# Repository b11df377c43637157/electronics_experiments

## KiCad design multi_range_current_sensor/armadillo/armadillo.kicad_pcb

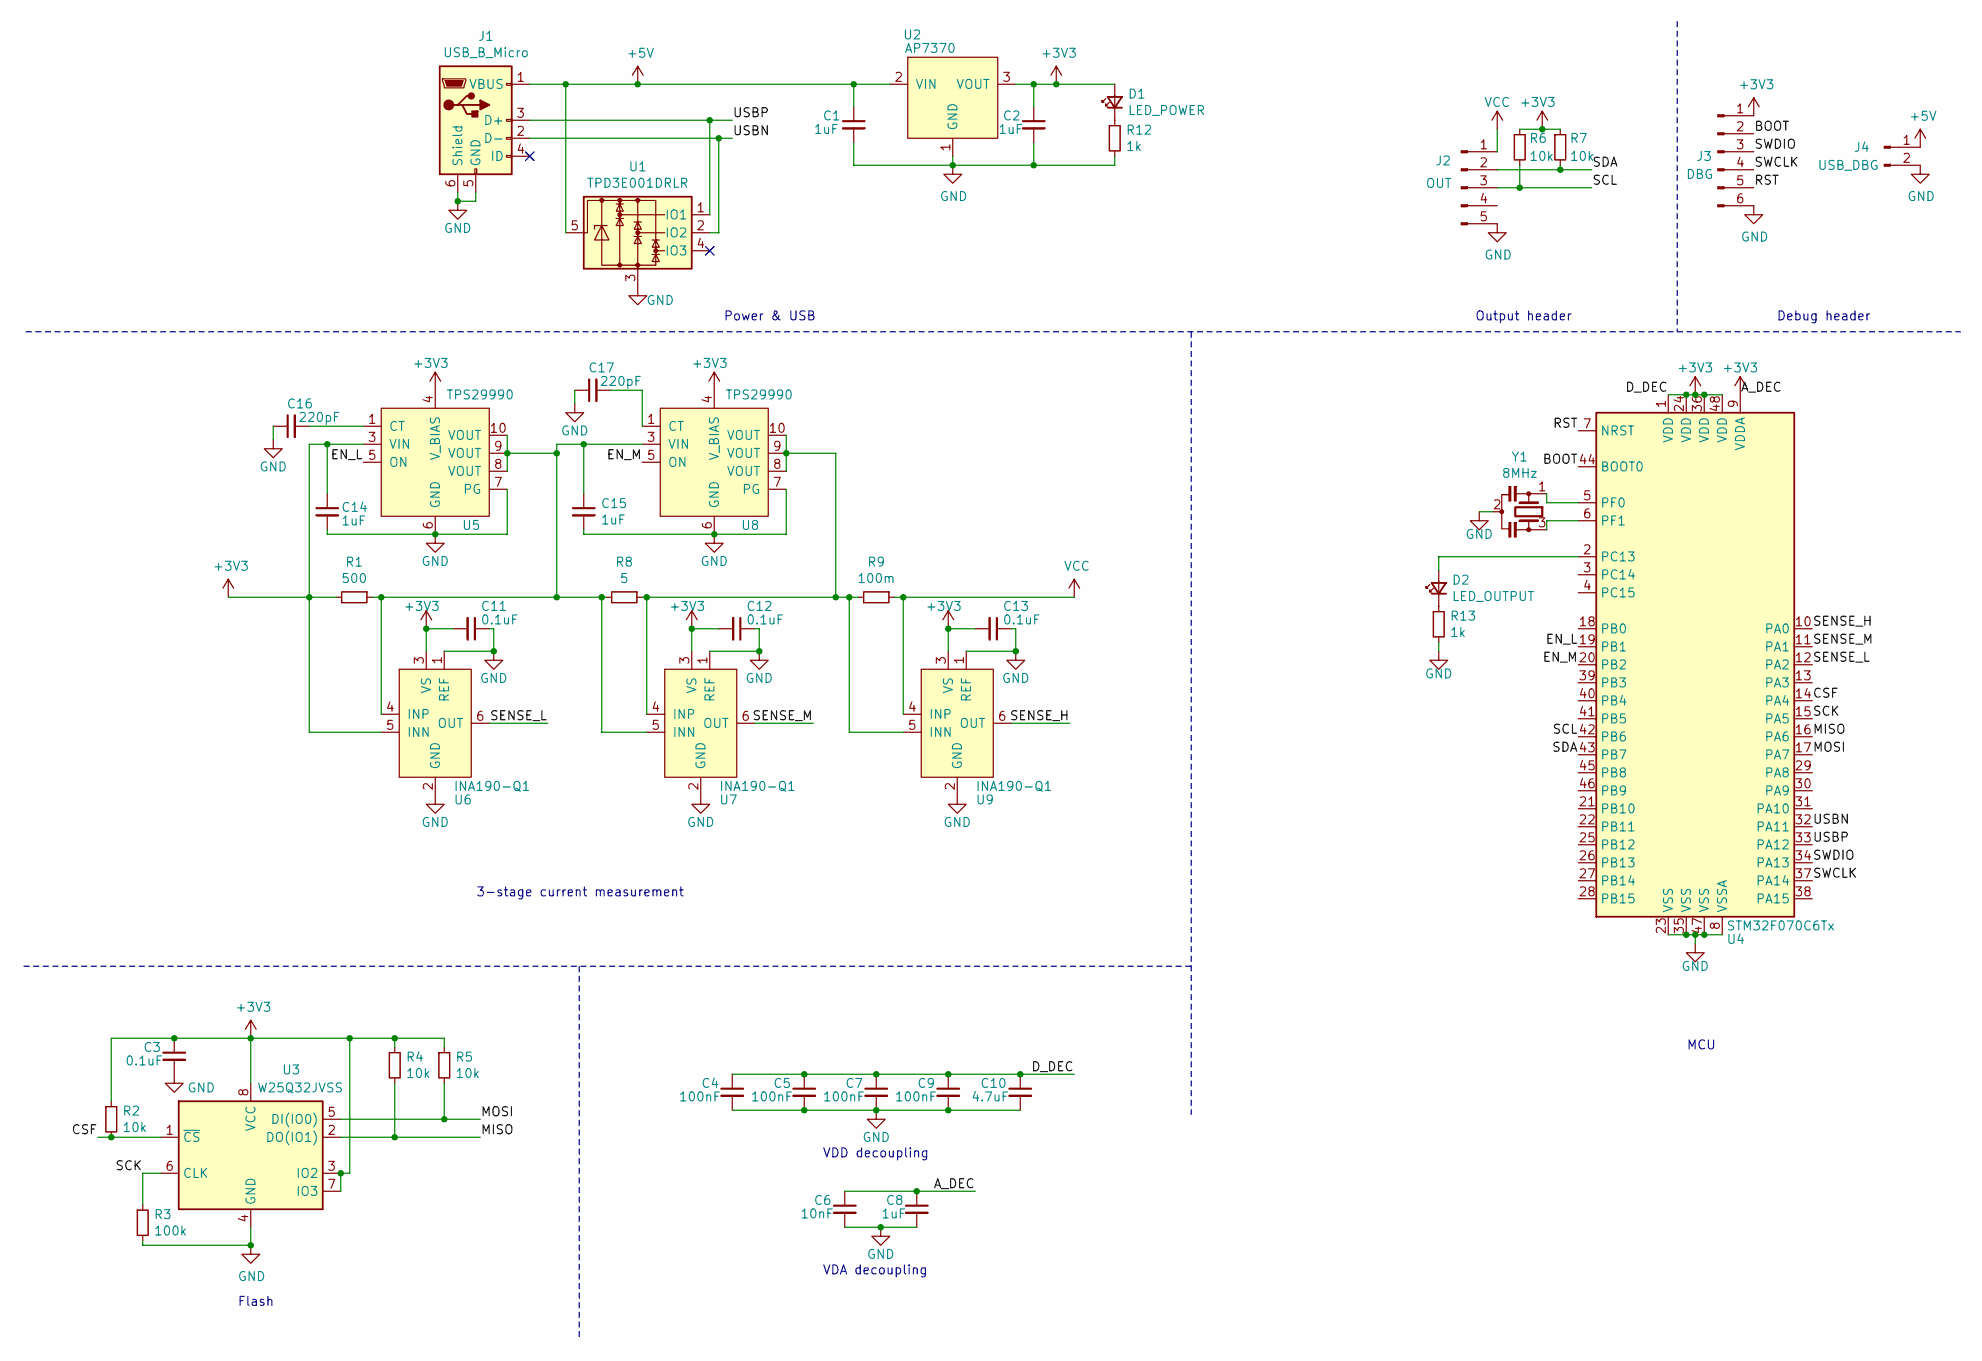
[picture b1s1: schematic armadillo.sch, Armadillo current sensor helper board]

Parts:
C1, C2, C8, C14, C15: 1uF; C_0603_1608Metric_Pad1.05x0.95mm_HandSolder
C3, C11, C12, C13: 0.1uF; C_0603_1608Metric_Pad1.05x0.95mm_HandSolder
C4, C5, C7, C9: 100nF; C_0603_1608Metric_Pad1.05x0.95mm_HandSolder
C6: 10nF; C_0603_1608Metric_Pad1.05x0.95mm_HandSolder
C10: 4.7uF; C_0603_1608Metric_Pad1.05x0.95mm_HandSolder
C16, C17: 220pF; C_0603_1608Metric_Pad1.05x0.95mm_HandSolder
D1: LED_POWER; LED_0603_1608Metric_Pad1.05x0.95mm_HandSolder
D2: LED_OUTPUT; LED_0603_1608Metric_Pad1.05x0.95mm_HandSolder
J1: USB_B_Micro; USB_Micro-B_Molex_47346-0001
J2: OUT; PinHeader_1x05_P2.54mm_Vertical
J3: DBG; PinHeader_1x06_P2.54mm_Vertical
J4: USB_DBG; PinHeader_1x02_P2.54mm_Vertical
R1: 500; R_0603_1608Metric_Pad1.05x0.95mm_HandSolder
R2, R4, R5, R6, R7: 10k; R_0603_1608Metric_Pad1.05x0.95mm_HandSolder
R3: 100k; R_0603_1608Metric_Pad1.05x0.95mm_HandSolder
R8: 5; R_0603_1608Metric_Pad1.05x0.95mm_HandSolder
R9: 100m; R_0603_1608Metric_Pad1.05x0.95mm_HandSolder
R12, R13: 1k; R_0603_1608Metric_Pad1.05x0.95mm_HandSolder
U1: TPD3E001DRLR; SOT-543
U2: AP7370; SOT-23-5_HandSoldering
U3: W25Q32JVSS; SOIC-8_5.23x5.23mm_P1.27mm
U4: STM32F070C6Tx; LQFP-48_7x7mm_P0.5mm
U5, U8: TPS29990; WSON-10-1EP_2x3mm_P0.5mm_EP0.84x2.4mm_ThermalVias
U6, U7, U9: INA190-Q1; SOT-363_SC-70-6_Handsoldering
Y1: 8MHz; Resonator_SMD_muRata_CSTxExxV-3Pin_3.0x1.1mm_HandSoldering

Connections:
+3V3: C2.1, C3.1, C4.1, C5.1, C6.1, C7.1, C8.1, C9.1, C10.1, C11.2, C12.2, C13.2, C14.1, D1.2 (A), J3.1, R1.2, R2.1, R4.1, R5.1, R6.1, R7.1, U2.3 (VOUT), U3.3 (IO2), U3.7 (IO3), U3.8 (VCC), U4.1 (VDD), U4.9 (VDDA), U4.24 (VDD), U4.36 (VDD), U4.48 (VDD), U5.3 (VIN), U5.4 (V_BIAS), U5.11, U6.3 (VS), U6.5 (INN), U7.3 (VS), U8.4 (V_BIAS), U9.3 (VS)
+5V: C1.1, J1.1 (VBUS), J4.1, U1.5, U2.2 (VIN)
/BOOT: J3.2, U4.44 (BOOT0)
/CSF: R2.2, U3.1 (~CS), U4.14 (PA4)
/EN_L: U4.19 (PB1), U5.5 (ON)
/EN_M: U4.20 (PB2), U8.5 (ON)
/MISO: R4.2, U3.2 (DO(IO1)), U4.16 (PA6)
/MOSI: R5.2, U3.5 (DI(IO0)), U4.17 (PA7)
/RST: J3.5, U4.7 (NRST)
/SCK: R3.1, U3.6 (CLK), U4.15 (PA5)
/SCL: J2.3, R6.2, U4.42 (PB6)
/SDA: J2.2, R7.2, U4.43 (PB7)
/SENSE_H: U4.10 (PA0), U9.6 (OUT)
/SENSE_L: U4.12 (PA2), U6.6 (OUT)
/SENSE_M: U4.11 (PA1), U7.6 (OUT)
/SWCLK: J3.4, U4.37 (PA14)
/SWDIO: J3.3, U4.34 (PA13)
/USBN: J1.2 (D-), U1.2 (IO2), U4.32 (PA11)
/USBP: J1.3 (D+), U1.1 (IO1), U4.33 (PA12)
GND: C1.2, C2.2, C3.2, C4.2, C5.2, C6.2, C7.2, C8.2, C9.2, C10.2, C11.1, C12.1, C13.1, C14.2, C15.2, C16.1, C17.1, J1.5 (GND), J1.6 (Shield), J2.5, J3.6, J4.2, R3.2, R12.2, R13.2, U1.3, U2.1 (GND), U3.4 (GND), U4.8 (VSSA), U4.23 (VSS), U4.35 (VSS), U4.47 (VSS), U5.6 (GND), U5.7 (PG), U6.1 (REF), U6.2 (GND), U7.1 (REF), U7.2 (GND), U8.6 (GND), U8.7 (PG), U9.1 (REF), U9.2 (GND), Y1.2
unnamed: C15.1, R1.1, R8.2, U5.8 (VOUT), U5.9 (VOUT), U5.10 (VOUT), U6.4 (INP), U7.5 (INN), U8.3 (VIN), U8.11
unnamed: C16.2, U5.1 (CT)
unnamed: C17.2, U8.1 (CT)
unnamed: D1.1 (K), R12.1
unnamed: D2.1 (K), R13.1
unnamed: D2.2 (A), U4.2 (PC13)
unnamed: R8.1, R9.2, U7.4 (INP), U8.8 (VOUT), U8.9 (VOUT), U8.10 (VOUT), U9.5 (INN)
unnamed: U4.5 (PF0), Y1.1
unnamed: U4.6 (PF1), Y1.3
VCC: J2.1, R9.1, U9.4 (INP)

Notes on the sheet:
Debug header
MCU
Output header
Flash
Power & USB
VDD decoupling
VDA decoupling
3-stage current measurement

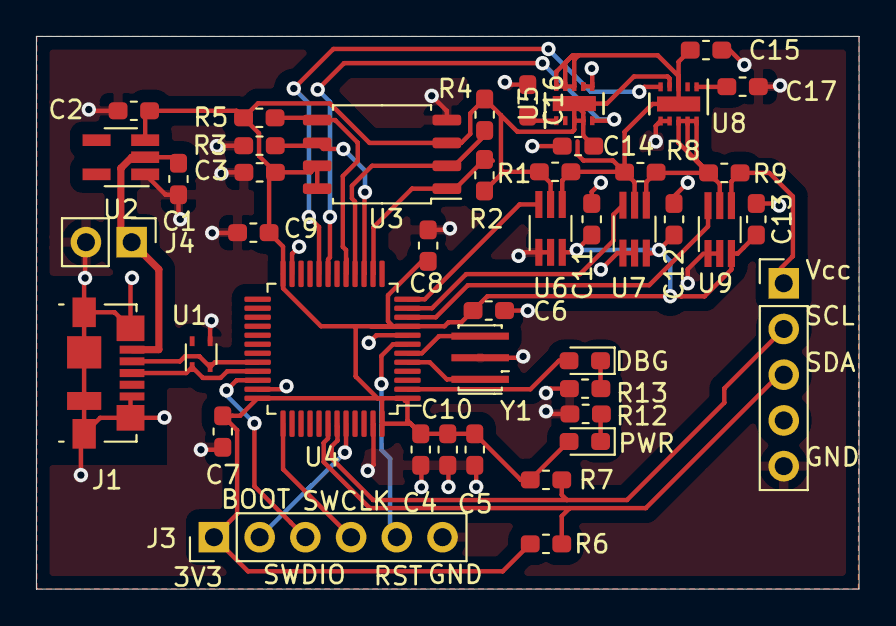
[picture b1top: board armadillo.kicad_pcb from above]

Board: 2 copper layers, 45.7 x 30.7 mm, 44 parts (0 on the bottom side), 30 nets.

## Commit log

2020-06-13 project: add new schematic for current sensor
    Attempt at creating a sensor that can measure dynamically changing
    current from ~1uA to 300 mA.
2020-06-14 current sense: add notebook for resistor size calculation
2020-06-20 current sensor: update schematic
2020-06-20 current sense: add screenshots
2020-06-20 current sense: add kicad project
2020-06-21 current sense: swap top GND for Vcc plane
2020-11-21 stm32_nrf24: add new board
